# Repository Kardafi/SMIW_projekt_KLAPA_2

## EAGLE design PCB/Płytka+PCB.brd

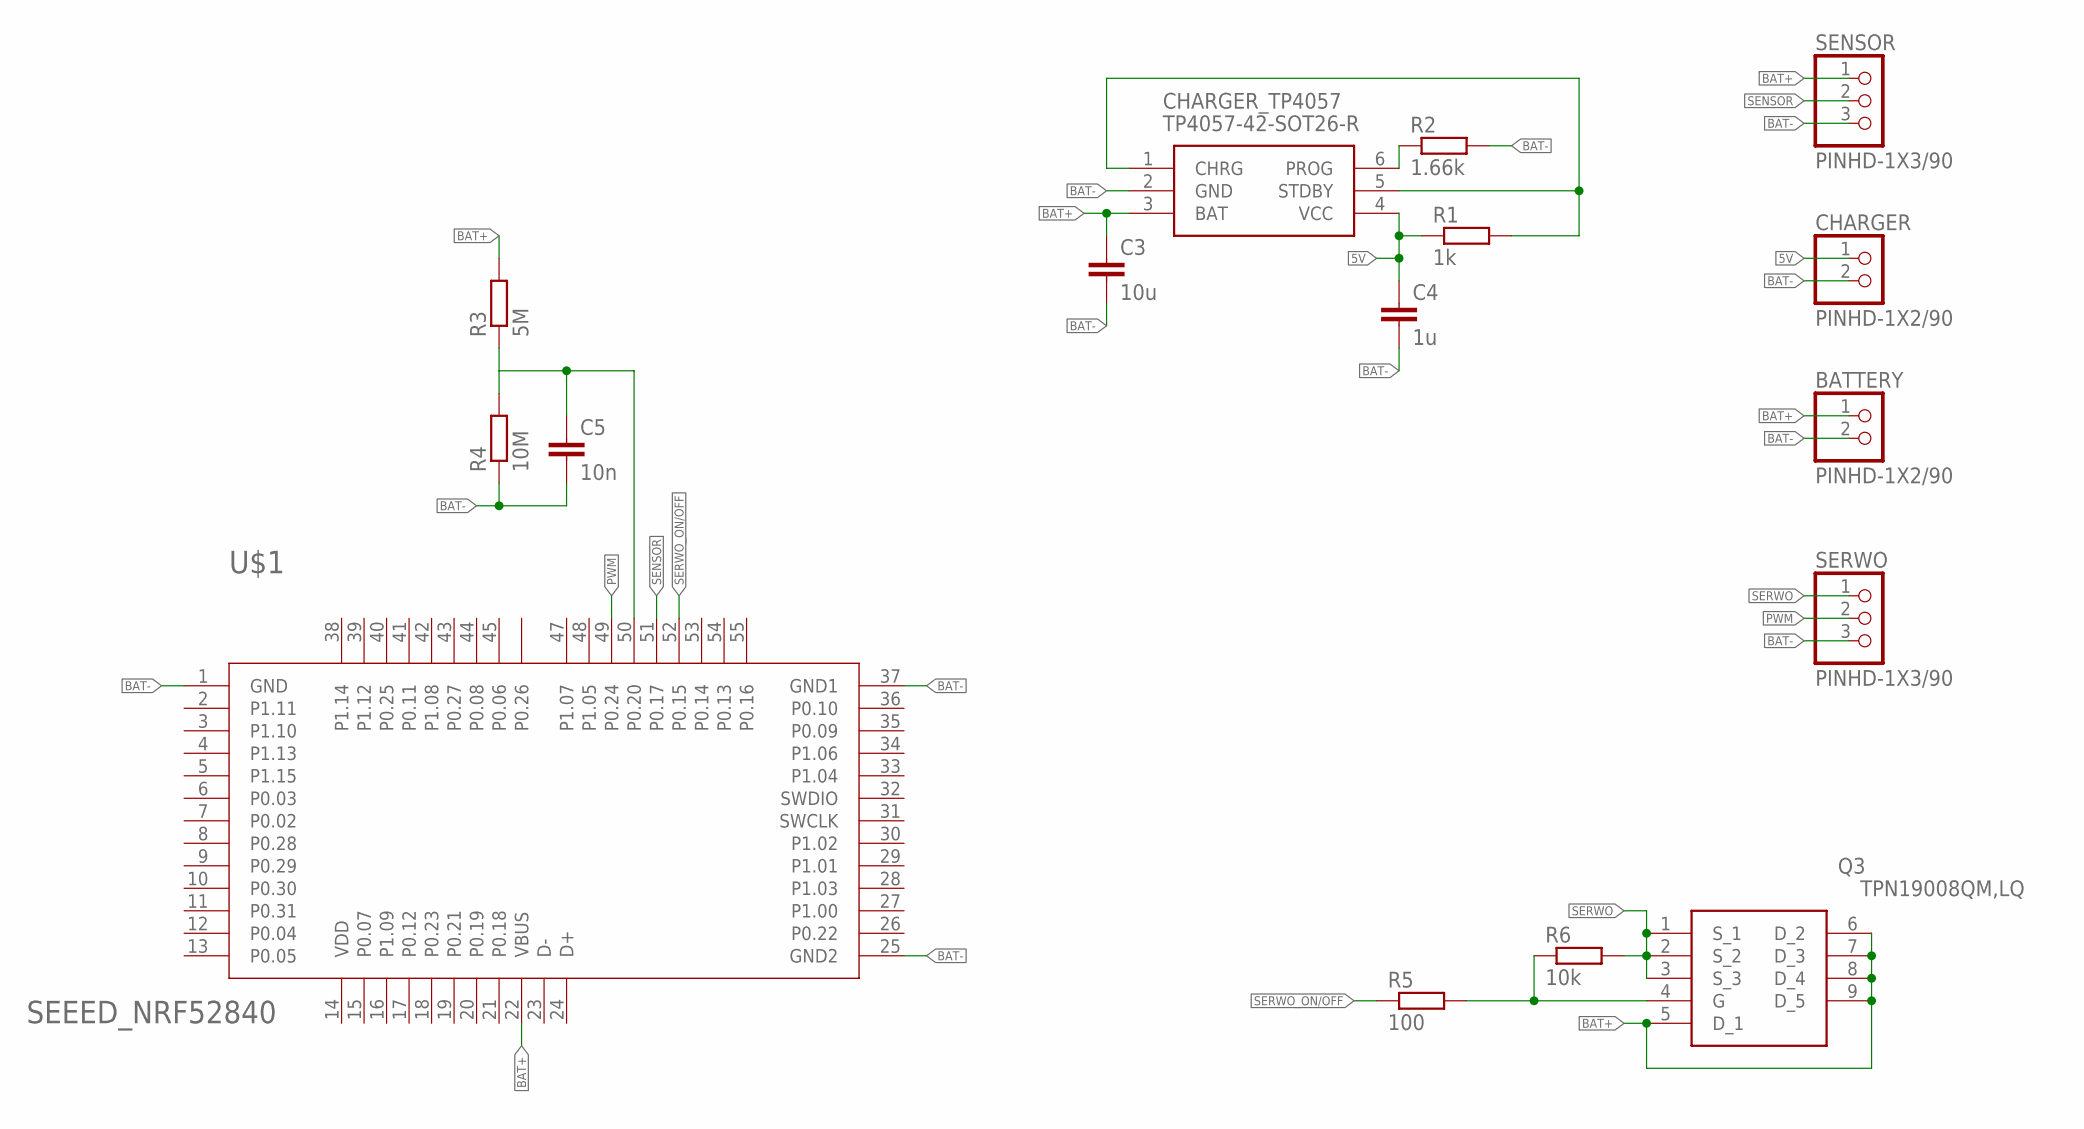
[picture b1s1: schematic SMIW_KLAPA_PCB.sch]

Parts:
BATTERY: PINHD-1X2/90; 1X02/90
C3: 10u; C01005
C4: 1u; C01005
C5: 10n; C01005
CHARGER: PINHD-1X2/90; 1X02/90
CHARGER_TP4057: TP4057-42-SOT26-R; SOT95P280X125-6N
Q3: TPN19008QM,LQ; TPN2R304PLL1Q
R1: 1k; R01005
R2: 1.66k; R01005
R3: 5M; R01005
R4: 10M; R01005
R5: 100; R01005
R6: 10k; R01005
SENSOR: PINHD-1X3/90; 1X03/90
SERWO: PINHD-1X3/90; 1X03/90
U$1: SEEED_NRF52840

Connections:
5V: C4.1, CHARGER.1, CHARGER_TP4057.4 (VCC), R1.1
BAT+: BATTERY.1, C3.1, CHARGER_TP4057.3 (BAT), Q3.5 (D_1), Q3.6 (D_2), Q3.7 (D_3), Q3.8 (D_4), Q3.9 (D_5), R3.2, SENSOR.1, U$1.22 (VBUS)
BAT-: BATTERY.2, C3.2, C4.2, C5.2, CHARGER.2, CHARGER_TP4057.2 (GND), R2.2, R4.1, SENSOR.3, SERWO.3, U$1.1 (GND), U$1.25 (GND2), U$1.37 (GND1)
unnamed: Q3.4 (G), R5.2, R6.1
unnamed: C5.1, R3.1, R4.2, U$1.7 (P0.02), U$1.50 (P0.20)
unnamed: CHARGER_TP4057.6 (PROG), R2.1
unnamed: CHARGER_TP4057.1 (CHRG), CHARGER_TP4057.5 (STDBY), R1.2
PWM: SERWO.2, U$1.49 (P0.24)
SENSOR: SENSOR.2, U$1.51 (P0.17)
SERWO: Q3.1 (S_1), Q3.2 (S_2), Q3.3 (S_3), R6.2, SERWO.1
SERWO_ON/OFF: R5.1, U$1.52 (P0.15)

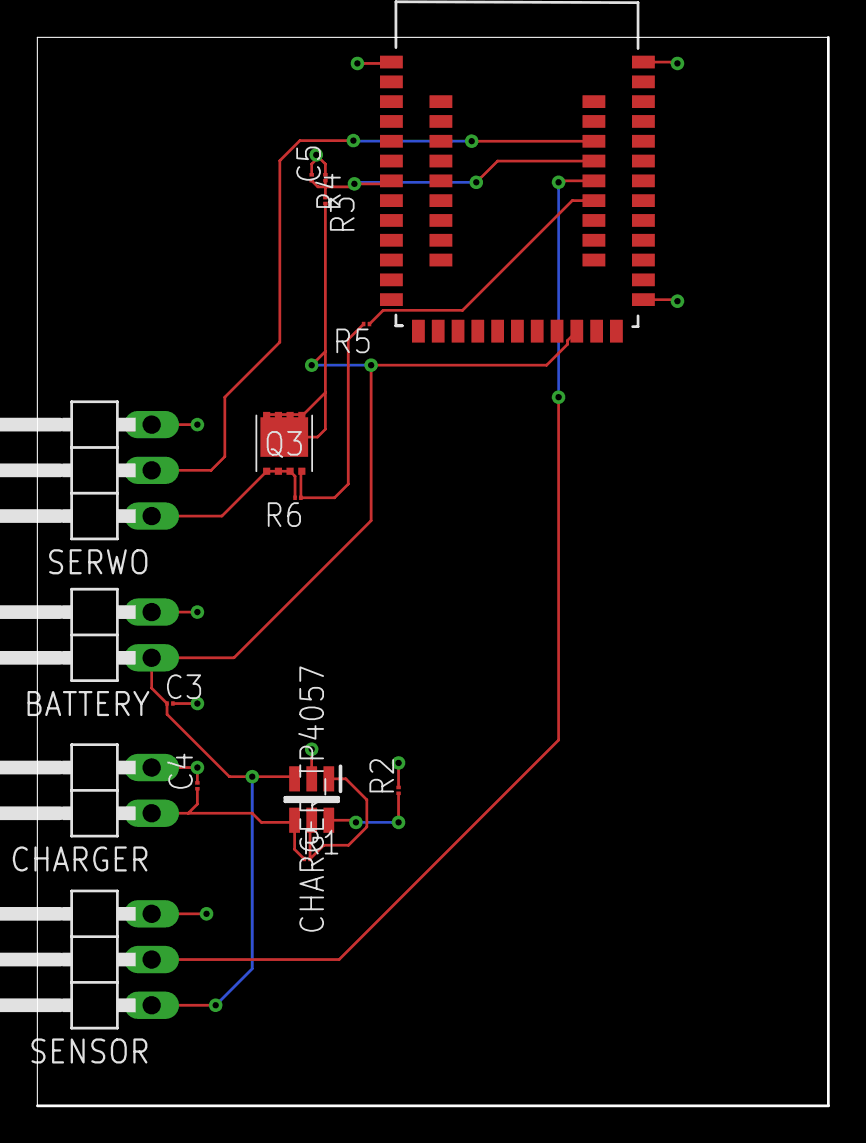
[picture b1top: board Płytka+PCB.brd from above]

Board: 2 copper layers, 43.9 x 59.4 mm, 16 parts (0 on the bottom side), 11 nets.

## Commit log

2024-02-18 nrf projekt
    nrf projekt
2024-02-18 android app
    android app
2024-02-18 pliki pcb
    pliki pcb
